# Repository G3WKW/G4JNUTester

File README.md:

# G4JNUTester
Simple tester for short circuit checking without damaging sensitive components.

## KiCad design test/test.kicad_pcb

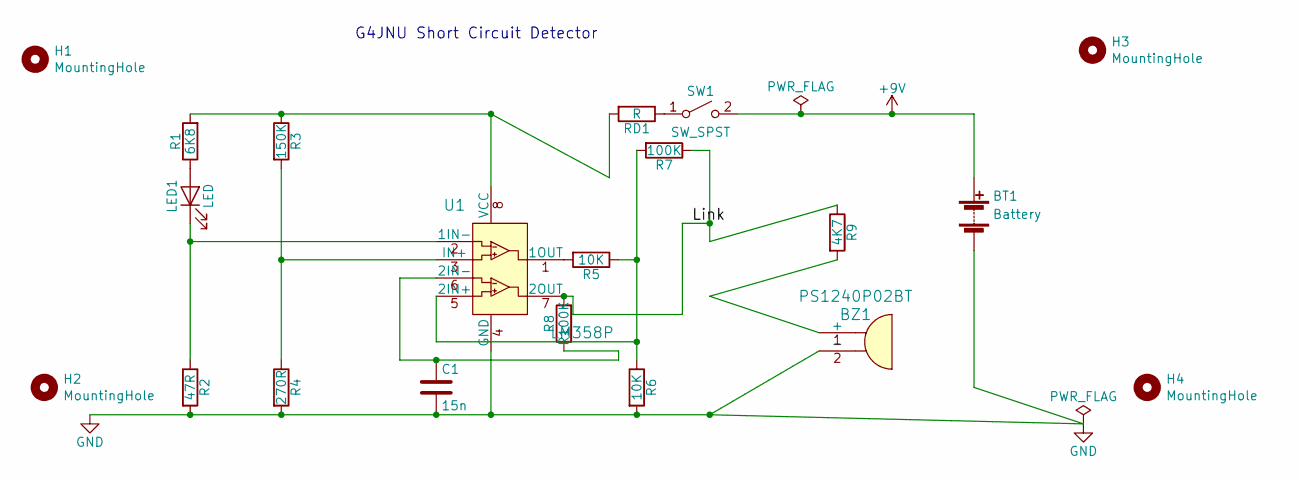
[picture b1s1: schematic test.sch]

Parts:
BT1: Battery; Pin_Header_Angled_1x02_Pitch2.54mm
BZ1: PS1240P02BT; Piezo_Transducer_THT_PS1240P02BT; MPN PS1240P02BT; Digi-Key_PN 445-2525-1-ND
C1: 15n; C_Axial_L3.8mm_D2.6mm_P10.00mm_Horizontal
H1, H2, H3, H4: MountingHole; MountingHole_2.2mm_M2
LED1: LED; LED_D1.8mm_W1.8mm_H2.4mm_Horizontal_O1.27mm_Z1.6mm
R1: 6K8; R_Axial_DIN0204_L3.6mm_D1.6mm_P5.08mm_Horizontal
R2: 47R; R_Axial_DIN0204_L3.6mm_D1.6mm_P5.08mm_Horizontal
R3: 150K; R_Axial_DIN0204_L3.6mm_D1.6mm_P5.08mm_Horizontal
R4: 270R; R_Axial_DIN0204_L3.6mm_D1.6mm_P5.08mm_Horizontal
R5, R6: 10K; R_Axial_DIN0204_L3.6mm_D1.6mm_P5.08mm_Horizontal
R7: 100K; R_Axial_DIN0204_L3.6mm_D1.6mm_P5.08mm_Horizontal
R8: R100K; R_Axial_DIN0204_L3.6mm_D1.6mm_P5.08mm_Horizontal
R9: 4K7; R_Axial_DIN0204_L3.6mm_D1.6mm_P5.08mm_Horizontal
RD1: R; D_5KPW_P12.70mm_Horizontal
SW1: SW_SPST; Switch
U1: LM358P; DIP-8_W7.62mm; MPN LM358P; Digi-Key_PN 296-1395-5-ND

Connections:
+9V: BT1.1 (+), SW1.2 (B)
/Link: R7.1, R8.2, R9.1, U1.7 (2OUT)
GND: BT1.2 (-), BZ1.2 (-), C1.2, R2.2, R4.2, R6.2, U1.4 (GND)
unnamed: BZ1.1 (+), R9.2
unnamed: C1.1, R8.1, U1.6 (2IN-)
unnamed: LED1.1 (K), R2.1, U1.2 (1IN-)
unnamed: LED1.2 (A), R1.1
unnamed: R1.2, R3.1, RD1.2, U1.8 (VCC)
unnamed: R3.2, R4.1, U1.3 (IN+)
unnamed: R5.1, R6.1, R7.2, U1.5 (2IN+)
unnamed: R5.2, U1.1 (1OUT)
unnamed: RD1.1, SW1.1 (A)

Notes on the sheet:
G4JNU Short Circuit Detector

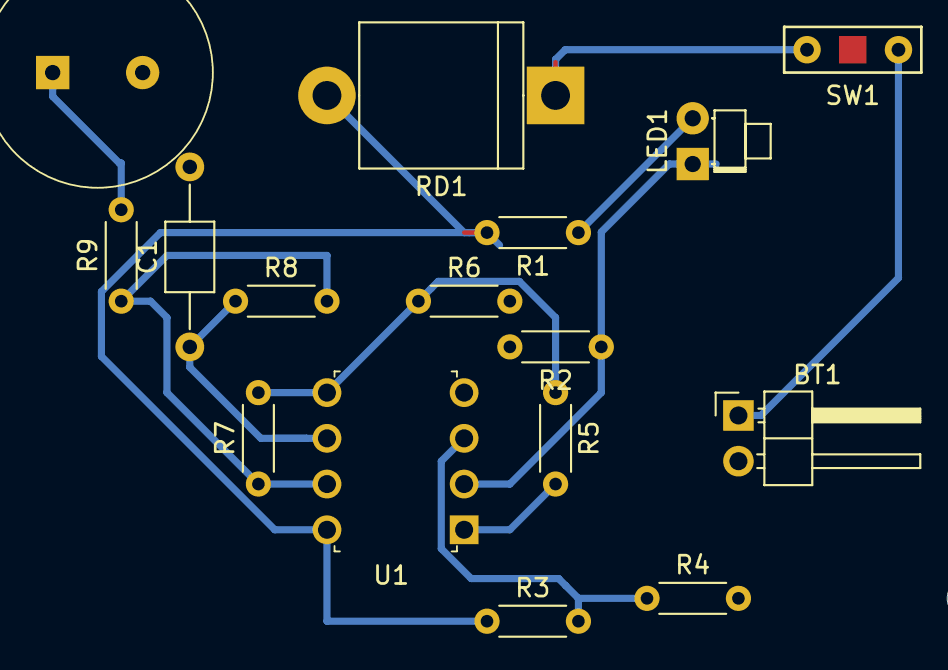
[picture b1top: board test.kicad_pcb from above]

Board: 2 copper layers, 20 parts (0 on the bottom side), 12 nets.

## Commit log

2018-09-28 Updated during construction evening
2018-09-28 Trying out 5.0
2019-02-11 Updated 7/2/20119 during meeting at RRFC
